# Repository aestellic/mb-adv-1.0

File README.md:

# 

> [!WARNING]
> This project is a work-in-progress and is currently incomplete.

> [!WARNING]
> The mb_adv is only compatible with certain devices. See [COMPATIBILITY.md](https://github.com/aestellic/mb-adv-firmware/blob/main/COMPATIBILITY.md) in the firmware repo for more info.

The mb_adv is a dongle for your GBA which injects multiboot ROMs via link cable.

With it, you can do stuff like [shiny hunt Jirachi without being tethered to a Gamecube](https://bsky.app/profile/cozydelaney.standingintheodds.com/post/3mt42ccd4bk23), boot [Poké Transporter GB](https://github.com/Striaton-Lab-Team/Poke_Transporter_GB), and even [connect your GBA to the internet](https://gblink.io/)!

If you'd like to buy one and are located in the USA, you can visit my store here (link will be added when store goes live). Otherwise, please see [MANUFACTURING.md](MANUFACTURING.md) for how to build one yourself!

# Usage
See [SETUP.md](https://github.com/aestellic/mb-adv-firmware/blob/main/SETUP.md) in the firmware repo.

# F.A.Q.
How does this differ from the GB-Link?

- While the GB-Link needs to be connected to a computer/phone to work, the mb_adv draws power directly from the GBA. This lets the mb_adv work without plugging into any external devices!

What does mb_adv stand for?

- It stands for multiboot advance.

What the heck is a multiboot?

- It's a small GBA program that can be sent over the link cable. This is the same system that multiplayer games which only required one cartridge use. It's also used for a lot of Pokémon distributions!

How did you make this?

# Credits
This project would not have been possible without the following people:
- [cozydelaney](https://bsky.app/profile/cozydelaney.standingintheodds.com), who designed the logo and provided so much emotional support <3
- [Ashton Herron (Starlark)](https://github.com/starlarkus), who guided me through the planning stages of the mb_adv.
- [prof.beans](https://www.thebeanlabs.com/), who designed the enclosure for the mb_adv.
- [Bucket Mouse](https://github.com/MouseBiteLabs), who helped with choosing components and designing the schematic and PCB.
- wheat jerm, who helped with designing the schematic and PCB.
- [The GB-Link Team](https://gblink.io/), who created the incredible GB-Link and [GB-Link firmware](https://github.com/GB-Link/GBLink-Firmware).
- [loopj](https://github.com/loopj/gba-link-port), who created the footprint and 3D model for the male GBA link cable connector.
- [zaksabeast](https://github.com/zaksabeast/Portable-Pico-Multibooter), who served as the inspiration and foundation for this project
> Note: the mb_adv is not endorsed by zaksabeast in any way, shape, or form.

# License
This project is fully open sourced under the [MIT License](LICENSE).

# Technical References
See [MANUFACTURING.md](MANUFACTURING.md) and [SCHEMATIC.pdf](SCHEMATIC.pdf)

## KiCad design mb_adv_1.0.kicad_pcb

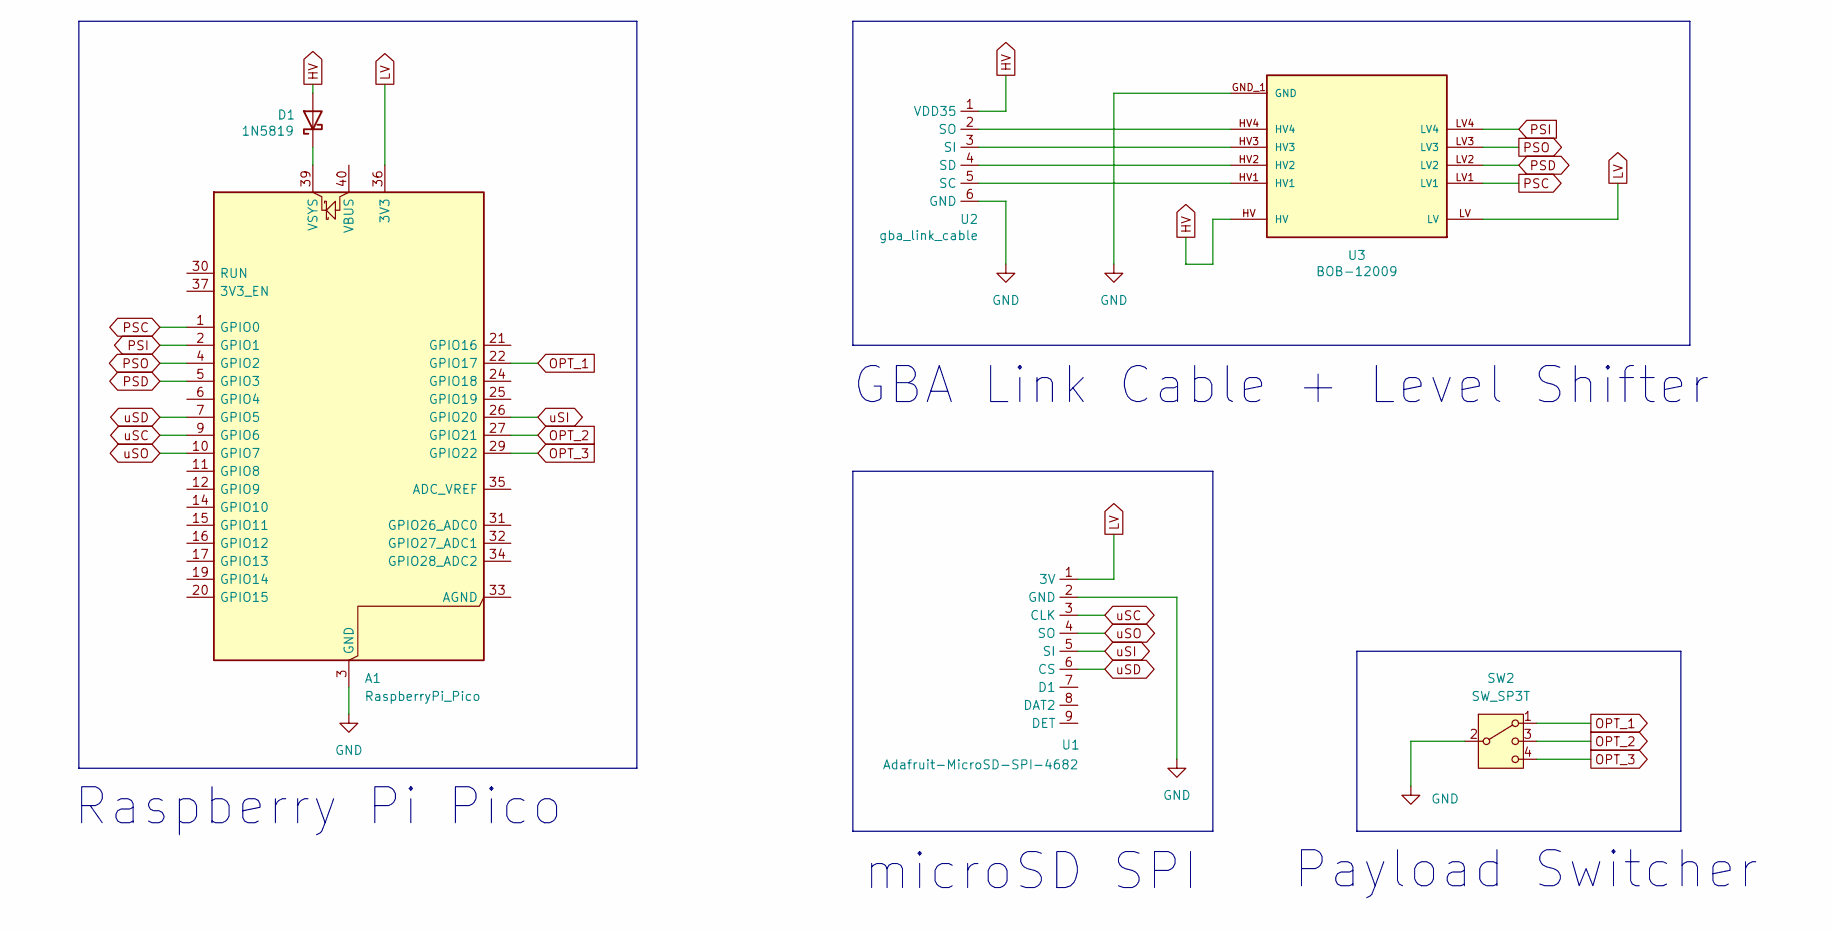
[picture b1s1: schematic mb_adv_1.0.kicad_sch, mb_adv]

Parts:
A1: RaspberryPi_Pico; RaspberryPi_Pico_Common_THT
D1: 1N5819; D_DO-41_SOD81_P10.16mm_Horizontal
SW2: SW_SP3T; DIP4_SP3T-TOP_4P3X8P6_CNK; MPN OS103011MS8QP1
U1: Adafruit-MicroSD-SPI-4682; adafruit_4682
U2: gba_link_cable; GBALinkPort_Male
U3: BOB-12009; CONV_BOB-12009; PARTREV 01

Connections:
GND: A1.3 (GND), A1.8 (GND), A1.13 (GND), A1.18 (GND), A1.23 (GND), A1.28 (GND), A1.38 (GND), SW2.2, U1.2 (GND), U2.6 (GND), U3.GND_1 (GND), U3.GND_2 (GND)
HV: D1.2 (A), U2.1 (VDD35), U3.HV
LV: A1.36 (3V3), U1.1 (3V), U3.LV
unnamed: A1.39 (VSYS), D1.1 (K)
unnamed: U2.5 (SC), U3.HV1
unnamed: U2.4 (SD), U3.HV2
unnamed: U2.3 (SI), U3.HV3
unnamed: U2.2 (SO), U3.HV4
OPT_1: A1.22 (GPIO17), SW2.1
OPT_2: A1.27 (GPIO21), SW2.3
OPT_3: A1.29 (GPIO22), SW2.4
PSC: A1.1 (GPIO0), U3.LV1
PSD: A1.5 (GPIO3), U3.LV2
PSI: A1.2 (GPIO1), U3.LV4
PSO: A1.4 (GPIO2), U3.LV3
uSC: A1.9 (GPIO6), U1.3 (CLK)
uSD: A1.7 (GPIO5), U1.6 (CS)
uSI: A1.26 (GPIO20), U1.5 (SI)
uSO: A1.10 (GPIO7), U1.4 (SO)

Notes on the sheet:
GBA Link Cable + Level Shifter
Payload Switcher
microSD SPI
Raspberry Pi Pico

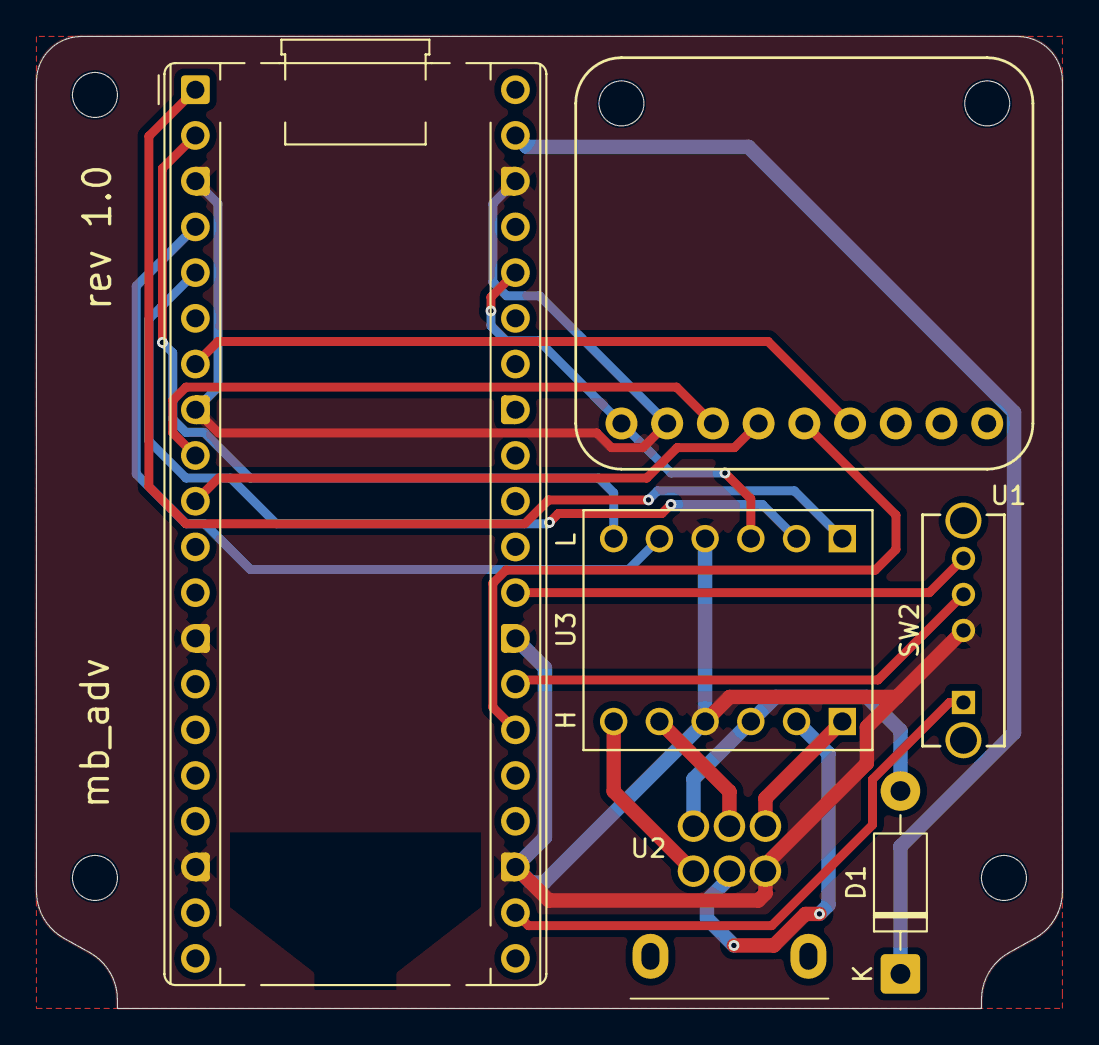
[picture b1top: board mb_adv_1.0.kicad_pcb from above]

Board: 2 copper layers, 57.0 x 54.0 mm, 9 parts (0 on the bottom side), 19 nets.

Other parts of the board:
M2.5, M2.5#2, M2.5#3: MountingHole_2.5mm
